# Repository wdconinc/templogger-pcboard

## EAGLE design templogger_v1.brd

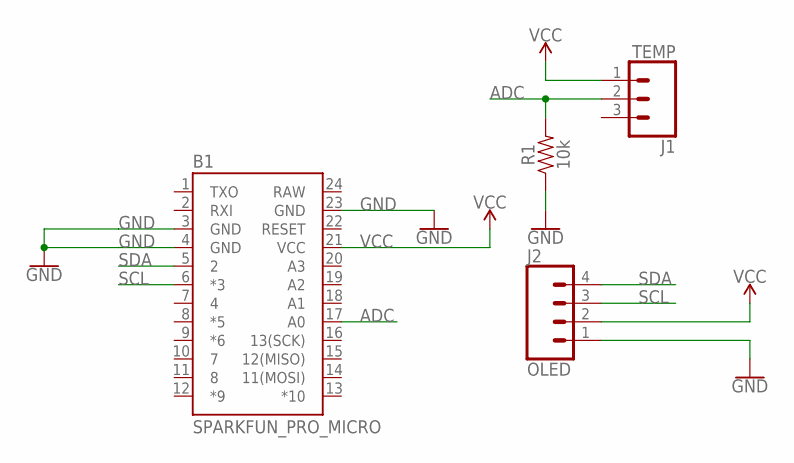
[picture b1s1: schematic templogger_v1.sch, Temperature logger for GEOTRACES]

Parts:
B1: SPARKFUN_PRO_MICRO
J1: TEMP; 1X03
J2: OLED; 1X04
R1: 10k; AXIAL-0.3

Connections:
ADC: B1.17 (A0), J1.2, R1.P$2 (2)
GND: B1.3 (GND), B1.4 (GND), B1.23 (GND), J2.1, R1.P$1 (1)
RAW: B1.24 (RAW)
SCL: B1.6 (*3), J2.3
SDA: B1.5 (2), J2.4
VCC: B1.21 (VCC), J1.1, J2.2

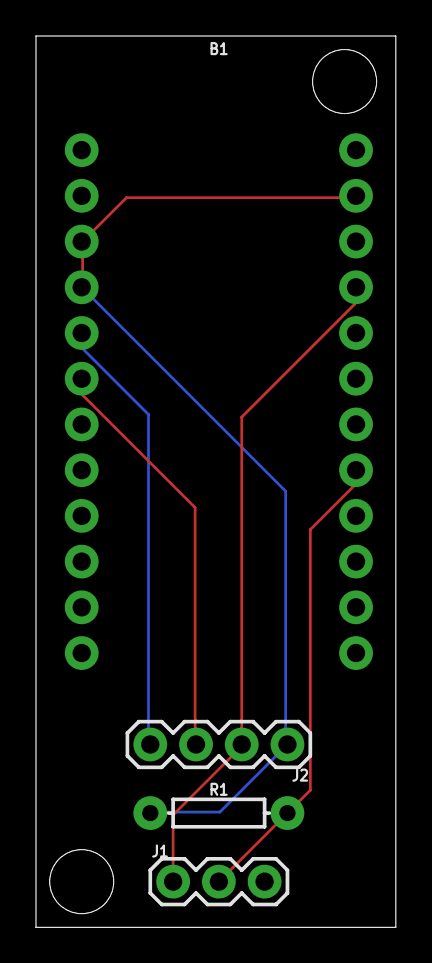
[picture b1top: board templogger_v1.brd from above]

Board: 2 copper layers, 20.0 x 49.5 mm, 4 parts (0 on the bottom side), 5 nets.

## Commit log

2018-08-22 Templogger board, v1

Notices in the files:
parts and their libraries:
SparkFun-Boards: Licensing: Creative Commons ShareAlike 4.0 International - https://creativecommons.org/licenses/by-sa/4.0
